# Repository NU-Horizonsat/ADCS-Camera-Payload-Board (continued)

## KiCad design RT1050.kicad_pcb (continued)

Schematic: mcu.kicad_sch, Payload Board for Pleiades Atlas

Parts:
C58: 4.7uF; C_0201_0603Metric
C59, C60, C61: 100nF; C_0201_0603Metric
H1, H2: MountingHole
R22: 10k; R_0402_1005Metric
U1: MIMXRT1052CVJ5B; MAPBGA196_12X12

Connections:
CSI_DATA_2: U1.J14 (GPIO_AD_B1_15); also elsewhere on the board
CSI_DATA_3: U1.G12 (GPIO_AD_B1_14); also elsewhere on the board
CSI_DATA_4: U1.H11 (GPIO_AD_B1_13); also elsewhere on the board
CSI_DATA_5: U1.H12 (GPIO_AD_B1_12); also elsewhere on the board
CSI_DATA_6: U1.J13 (GPIO_AD_B1_11); also elsewhere on the board
CSI_DATA_7: U1.L13 (GPIO_AD_B1_10); also elsewhere on the board
CSI_DATA_8: U1.M13 (GPIO_AD_B1_09); also elsewhere on the board
CSI_DATA_9: U1.H13 (GPIO_AD_B1_08); also elsewhere on the board
CSI_HSYNC: U1.K10 (GPIO_AD_B1_07); also elsewhere on the board
CSI_MCLK: U1.K12 (GPIO_AD_B1_05); also elsewhere on the board
CSI_PIXCLK: U1.L12 (GPIO_AD_B1_04); also elsewhere on the board
CSI_VSYNC: U1.J12 (GPIO_AD_B1_06); also elsewhere on the board
EN_MAG: U1.C14 (GPIO_B1_14); also elsewhere on the board
GND: C58.2, C59.2, C60.2, C61.2, R22.2; also elsewhere on the board
GPIO_AD_B0_04: U1.F11 (GPIO_AD_B0_04); also elsewhere on the board
GPIO_AD_B0_05: U1.G14 (GPIO_AD_B0_05); also elsewhere on the board
GPIO_B0_04: U1.C8 (GPIO_B0_04); also elsewhere on the board
GPIO_B0_05: U1.B8 (GPIO_B0_05); also elsewhere on the board
GPIO_B0_06: U1.A8 (GPIO_B0_06); also elsewhere on the board
GPIO_B0_07: U1.A9 (GPIO_B0_07); also elsewhere on the board
GPIO_B0_08: U1.B9 (GPIO_B0_08); also elsewhere on the board
GPIO_B0_09: U1.C9 (GPIO_B0_09); also elsewhere on the board
GPIO_B0_10: U1.D9 (GPIO_B0_10); also elsewhere on the board
GPIO_B0_11: U1.A10 (GPIO_B0_11); also elsewhere on the board
GPIO_B0_12: U1.C10 (GPIO_B0_12); also elsewhere on the board
GPIO_B0_13: U1.D10 (GPIO_B0_13); also elsewhere on the board
GPIO_B0_14: U1.E10 (GPIO_B0_14); also elsewhere on the board
GPIO_B0_15: U1.E11 (GPIO_B0_15); also elsewhere on the board
JTAG_MOD: R22.1, U1.F13 (GPIO_AD_B0_08)
JTAG_TCK: U1.F12 (GPIO_AD_B0_07); also elsewhere on the board
JTAG_TDI: U1.F14 (GPIO_AD_B0_09); also elsewhere on the board
JTAG_TDO: U1.G13 (GPIO_AD_B0_10); also elsewhere on the board
JTAG_TMS: U1.E14 (GPIO_AD_B0_06); also elsewhere on the board
JTAG_TRSTB: U1.G10 (GPIO_AD_B0_11); also elsewhere on the board
LDO_EN: U1.B13 (GPIO_B1_10); also elsewhere on the board
LPI2C1_SCL: U1.J11 (GPIO_AD_B1_00); also elsewhere on the board
LPI2C1_SDA: U1.K11 (GPIO_AD_B1_01); also elsewhere on the board
LPI2C4_SCL: U1.K14 (GPIO_AD_B0_12); also elsewhere on the board
LPI2C4_SDA: U1.L14 (GPIO_AD_B0_13); also elsewhere on the board
LPSPI3_SCK: U1.M14 (GPIO_AD_B0_00); also elsewhere on the board
LPSPI3_SDI: U1.M11 (GPIO_AD_B0_02); also elsewhere on the board
LPSPI3_SDO: U1.H10 (GPIO_AD_B0_01); also elsewhere on the board
LPSPI4_SCK: U1.B12 (GPIO_B1_07); also elsewhere on the board
LPSPI4_SDI: U1.D12 (GPIO_B1_05); also elsewhere on the board
LPSPI4_SDO: U1.C12 (GPIO_B1_06); also elsewhere on the board
LPUART2_RX: U1.M12 (GPIO_AD_B1_03); also elsewhere on the board
LPUART2_TX: U1.L11 (GPIO_AD_B1_02); also elsewhere on the board
PH1_A_3: U1.E8 (GPIO_B0_02); also elsewhere on the board
PH1_B_3: U1.E7 (GPIO_B0_01); also elsewhere on the board
PH2_A_3: U1.D7 (GPIO_B0_00); also elsewhere on the board
PWDN: U1.C13 (GPIO_B1_11); also elsewhere on the board
PWM1_A_3: U1.A11 (GPIO_B1_00); also elsewhere on the board
PWM1_B_3: U1.B11 (GPIO_B1_01); also elsewhere on the board
PWM2_A_3: U1.C11 (GPIO_B1_02); also elsewhere on the board
SHDN: U1.A13 (GPIO_B1_09)
STB: U1.A12 (GPIO_B1_08)
WDT_ENABLE: U1.G11 (GPIO_AD_B0_03); also elsewhere on the board
WDT_WDI: U1.D14 (GPIO_B1_13); also elsewhere on the board
XRS: U1.D13 (GPIO_B1_12); also elsewhere on the board

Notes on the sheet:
SPI3 - Developement SPI4 - Developement I2C4 - Developement I2C1 - Sensors I2C3 - Camera UART2 - Debug UART3 - Developement (do not pull high during boot)

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
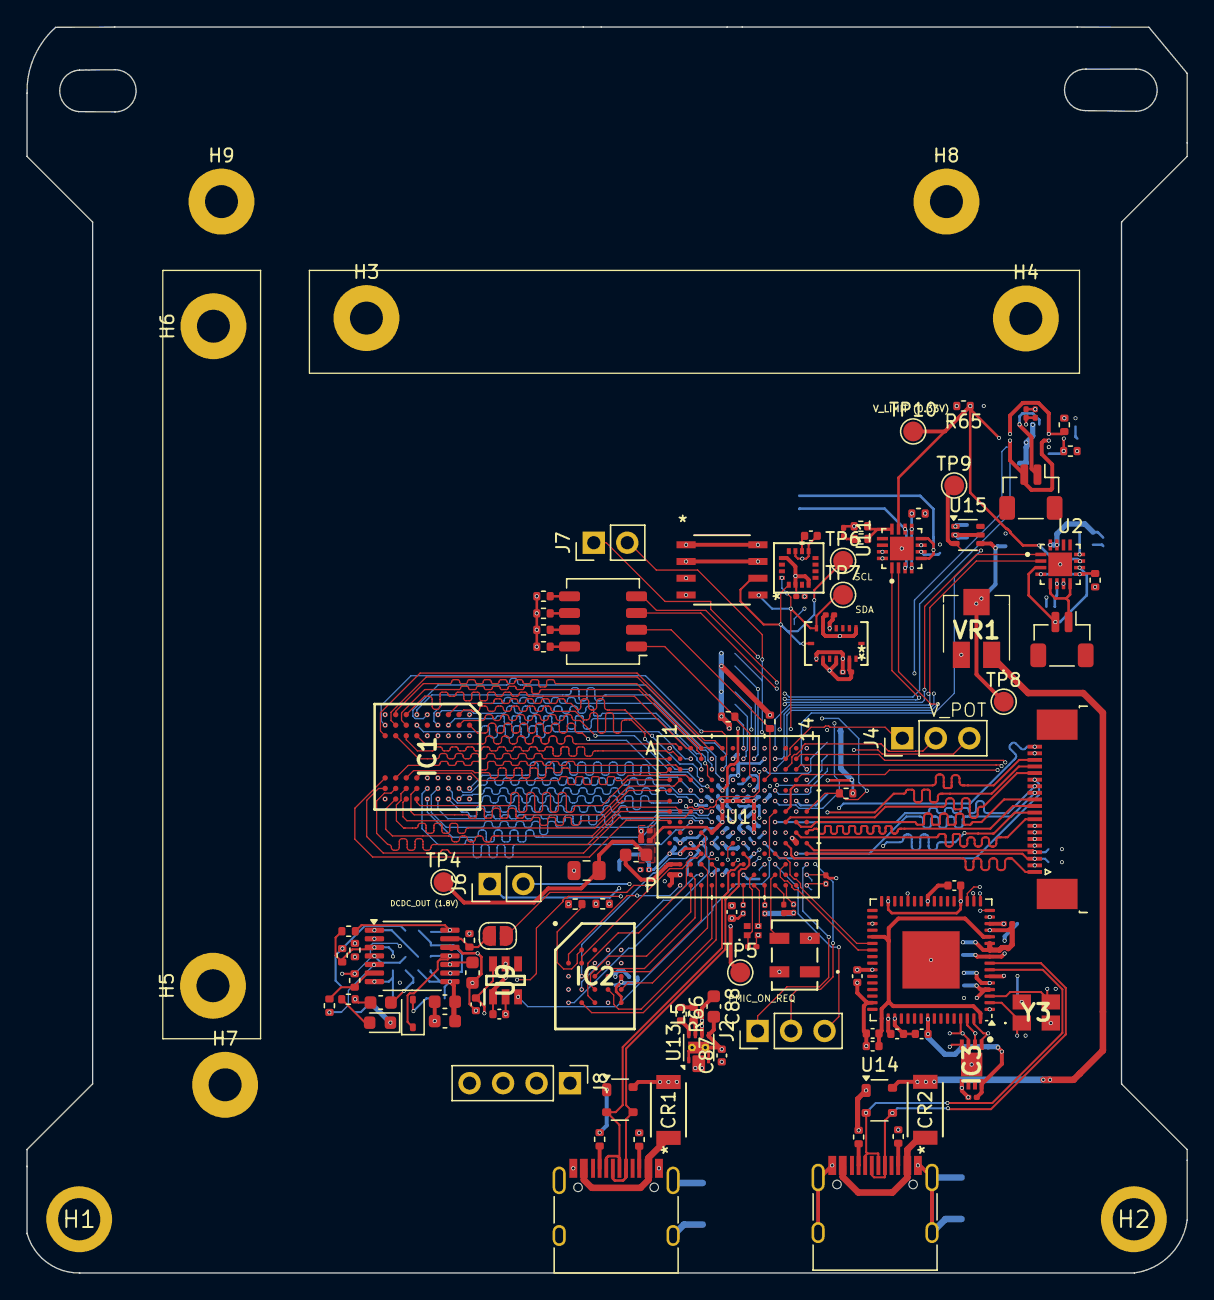
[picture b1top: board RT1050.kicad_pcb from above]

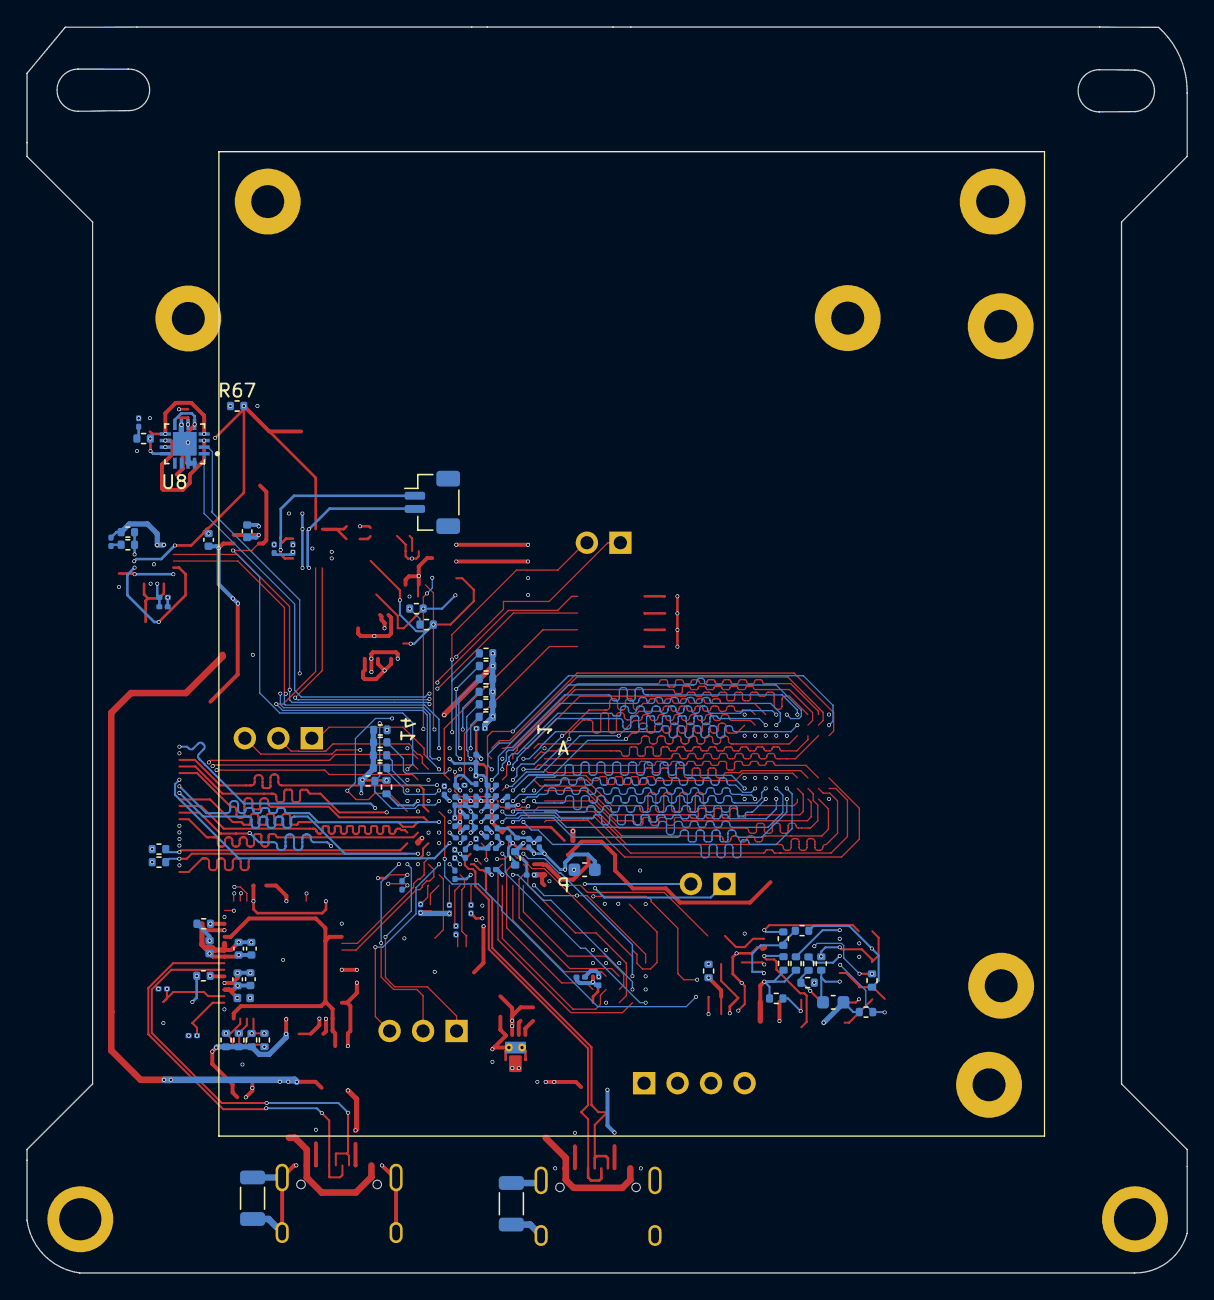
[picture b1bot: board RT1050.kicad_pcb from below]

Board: 4 copper layers, 88.0 x 94.5 mm, 212 parts (96 on the bottom side), 191 nets.

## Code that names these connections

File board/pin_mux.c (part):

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  - {pin_num: J14, peripheral: CSI, signal: 'csi_data, 02', pin_signal: GPIO_AD_B1_15}
  - {pin_num: F13, peripheral: CSI, signal: 'csi_data, 05', pin_signal: GPIO_AD_B0_08}
  - {pin_num: J13, peripheral: CSI, signal: 'csi_data, 06', pin_signal: GPIO_AD_B1_11}
  - {pin_num: G14, peripheral: CSI, signal: 'csi_data, 08', pin_signal: GPIO_AD_B0_05}
  - {pin_num: H13, peripheral: CSI, signal: 'csi_data, 09', pin_signal: GPIO_AD_B1_08}
  - {pin_num: J12, peripheral: CSI, signal: csi_vsync, pin_signal: GPIO_AD_B1_06}
  - {pin_num: L12, peripheral: CSI, signal: csi_pixclk, pin_signal: GPIO_AD_B1_04}
  - {pin_num: K12, peripheral: CSI, signal: csi_mclk, pin_signal: GPIO_AD_B1_05}
  - {pin_num: K10, peripheral: CSI, signal: csi_hsync, pin_signal: GPIO_AD_B1_07}
  - {pin_num: P3, peripheral: FLEXSPI, signal: FLEXSPI_A_DATA0, pin_signal: GPIO_SD_B1_08}
  - {pin_num: N4, peripheral: FLEXSPI, signal: FLEXSPI_A_DATA1, pin_signal: GPIO_SD_B1_09}
  - {pin_num: L3, peripheral: FLEXSPI, signal: FLEXSPI_A_SS0_B, pin_signal: GPIO_SD_B1_06}
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  - {pin_num: P2, peripheral: FLEXSPI, signal: FLEXSPI_B_SCLK, pin_signal: GPIO_SD_B1_04}
  - {pin_num: J11, peripheral: LPI2C1, signal: SCL, pin_signal: GPIO_AD_B1_00}
  - {pin_num: K11, peripheral: LPI2C1, signal: SDA, pin_signal: GPIO_AD_B1_01}
  - {pin_num: C8, peripheral: LPI2C2, signal: SCL, pin_signal: GPIO_B0_04}
  - {pin_num: B8, peripheral: LPI2C2, signal: SDA, pin_signal: GPIO_B0_05}
  - {pin_num: L14, peripheral: LPI2C4, signal: SDA, pin_signal: GPIO_AD_B0_13}
  - {pin_num: K14, peripheral: LPI2C4, signal: SCL, pin_signal: GPIO_AD_B0_12}
  - {pin_num: M14, peripheral: LPSPI3, signal: SCK, pin_signal: GPIO_AD_B0_00}
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
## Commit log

2025-03-09 v0.2
2025-03-23 started layout
2025-03-24 redid power rails to allow for sleep
2025-03-30 finished layout of v0.2!
2025-04-02 added testpoints
